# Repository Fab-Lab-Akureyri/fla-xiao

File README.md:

# fla-xiao

KiCad útgáfa af [fabxiao](https://fabacademy.org/2020/labs/leon/students/adrian-torres/fabxiao.html) eftir meistara [Adrián Torres](https://fabacademy.org/2020/labs/leon/students/adrian-torres/index.html).

## Breytingar

- [x] Notast við sökkla fyrir Xiao tölvunar
- [x] Rásum endurrað, hægt að fræsa með 0.4mm bita.
- [x] Íhlutum þjappað aðeins
- [x] .dxf skrá bætt við, hentug fyrir Xtool laser 

## BOM / Íhlutalisti

Hægt að nota 3+4 sökkla fyrir tölvuna eða klippa niður lengri sökkla. 

| Íhlutir               | Magn  |
| ---                   | ---   |
| FR1 bretti            | 1 stk | 
| [ESP32C3](https://www.digikey.fi/en/products/detail/seeed-technology-co-ltd/113991054/16652880) / [RP2040](https://www.digikey.com/en/products/detail/seeed-technology-co-ltd/102010428/14672129) | 1 stk |
| [0Ω](https://www.digikey.com/en/products/detail/yageo/RC1206FR-070RL/5698945) viðnám             | 1 stk |
| [499Ω](https://www.digikey.com/en/products/detail/yageo/RC1206FR-07499RL/728944) viðnám           | 1 stk |
| [1kΩ](https://www.digikey.com/en/products/detail/yageo/RC1206FR-071KL/728387) viðnám            | 1 stk |
| 1026 LED, t.d. [blá](https://www.digikey.com/en/products/detail/nextgen-components/1206BBD8100S01/14318403?s=N4IgjCBcoMwOxVAYygMwIYBsDOBTANCAPZQDaIMATAAwAstEAuoQA4AuUIAymwE4CWAOwDmIAL6EAtLUQgUkDDgLEyIAGwwArJpCMxEkJVVgaagASZcAEzPYAtld1igA)                   | 1 stk |
| [B3SN-takki](https://www.digikey.com/en/products/detail/omron-electronics-inc-emc-div/B3SN-3012/1811776?s=N4IgTCBcDaIM4HcCMSAsYC0A7AJiAugL5A)            | 1 stk |
| [Sökkull 4pos](https://www.digikey.com/en/products/detail/sullins-connector-solutions/NPTC041KFXC-RC/776054)          | 2 stk |
| [Sökkull 3pos](https://www.digikey.com/en/products/detail/sullins-connector-solutions/NPTC031KFXC-RC/776053)          | 2 stk |
| [90° tengi 8 pos](https://www.digikey.com/en/products/detail/samtec-inc/SMH-108-02-G-S/10218741)         | 1 stk |
| [90° tengi 5 pos](https://www.digikey.com/en/products/detail/samtec-inc/SMH-105-02-G-S/10218735) | 1 stk |
| [90° tengi 6 pos](https://www.digikey.com/en/products/detail/gct/BG300-06-A-L-A/9859597) | Hægt að nota í staði 5 pos |

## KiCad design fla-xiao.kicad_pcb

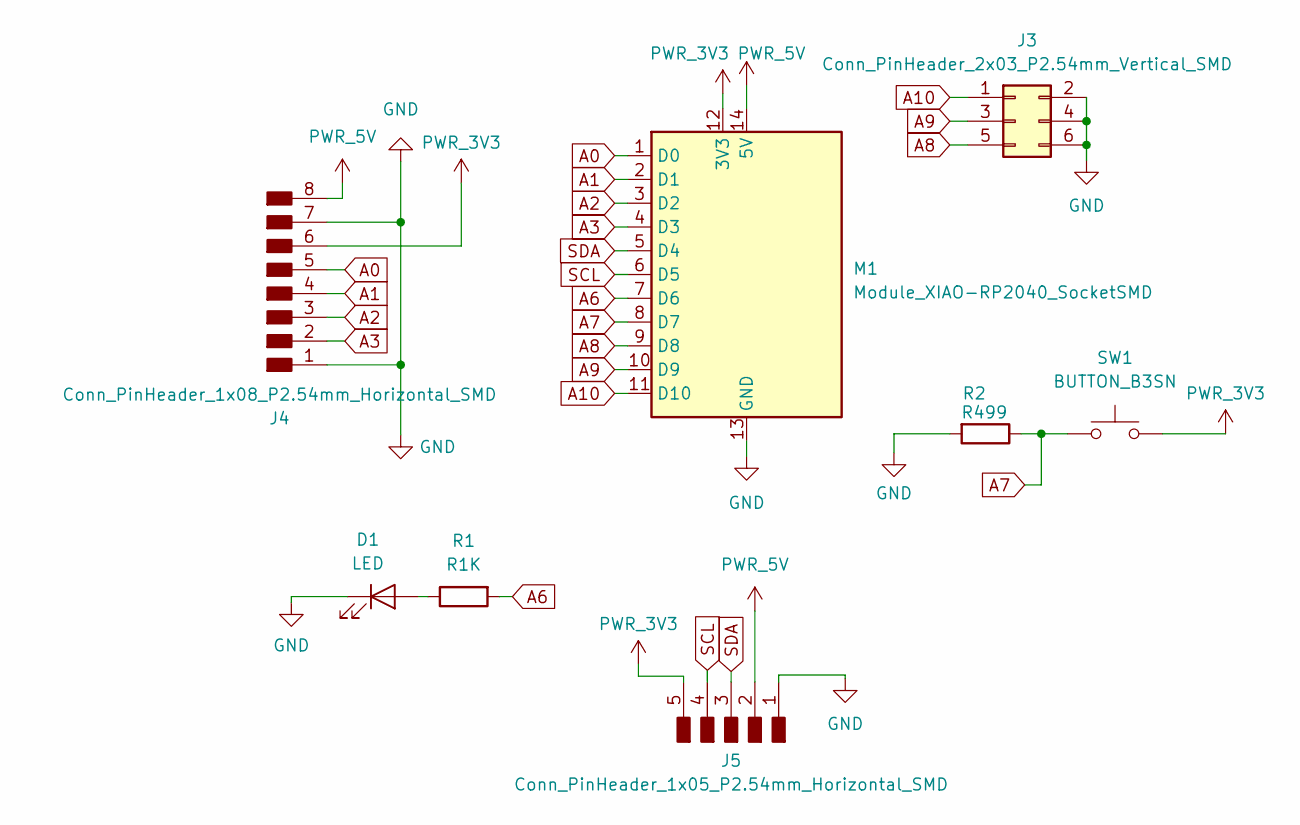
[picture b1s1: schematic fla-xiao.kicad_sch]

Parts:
D1: LED; LED_1206
J3: Conn_PinHeader_2x03_P2.54mm_Vertical_SMD; PinHeader_2x03_P2.54mm_Vertical_SMD
J4: Conn_PinHeader_1x08_P2.54mm_Horizontal_SMD; PinHeader_1x08_P2.54mm_Horizontal_SMD
J5: Conn_PinHeader_1x05_P2.54mm_Horizontal_SMD; PinHeader_1x05_P2.54mm_Horizontal_SMD
M1: Module_XIAO-RP2040_SocketSMD; SeeedStudio_XIAO_SocketSMD
R1: R1K; R_1206
R2: R499; R_1206
SW1: BUTTON_B3SN; Button_Omron_B3SN_6.0x6.0mm

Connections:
A0: J4.5, M1.1 (D0)
A1: J4.4, M1.2 (D1)
A2: J4.3, M1.3 (D2)
A3: J4.2, M1.4 (D3)
A6: M1.7 (D6), R1.2
A7: M1.8 (D7), R2.1, SW1.1
A8: J3.5, M1.9 (D8)
A9: J3.3, M1.10 (D9)
A10: J3.1, M1.11 (D10)
GND: D1.1 (K), J3.2, J3.4, J3.6, J4.1, J4.7, J5.1, M1.13 (GND), R2.2
unnamed: D1.2 (A), R1.1
PWR_3V3: J4.6, J5.5, M1.12 (3V3), SW1.2
PWR_5V: J4.8, J5.2, M1.14 (5V)
SCL: J5.4, M1.6 (D5)
SDA: J5.3, M1.5 (D4)

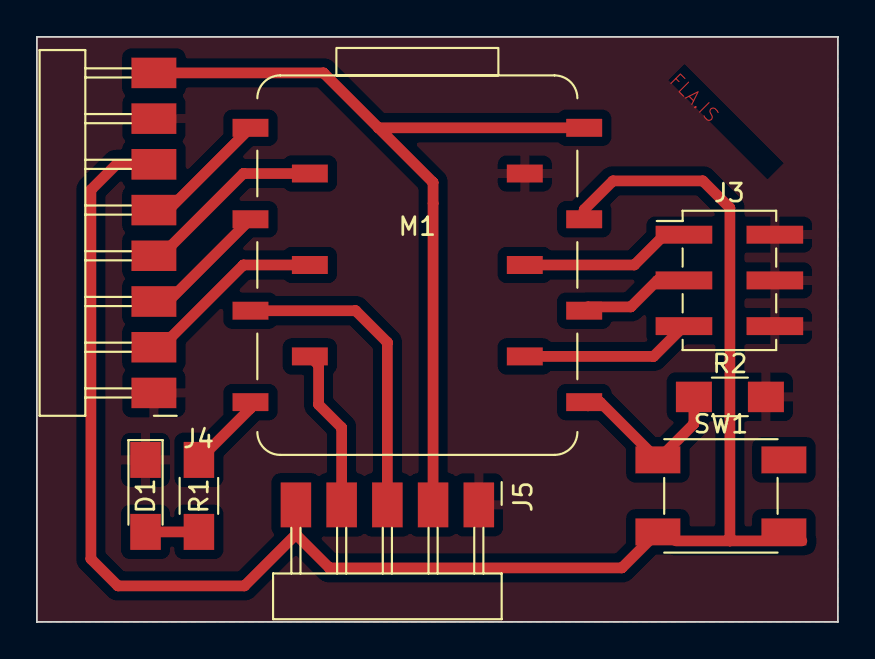
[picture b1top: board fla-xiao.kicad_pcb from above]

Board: 2 copper layers, 44.5 x 32.5 mm, 8 parts (0 on the bottom side), 15 nets.

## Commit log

2023-05-04 Added KiCAD project
2023-05-04 Added images
2023-05-08 Updated to use sockets with XIAO
2023-05-09 .\fla-xiao.kicad*
2023-05-09 Moved a couple of wires, need to clean up
2023-08-31 Updated board
2023-08-31 Updated images
2023-09-01 Fix trace, too close
2023-09-01 Adjust trace and updated image
2023-09-01 Added gerber files to .gitignore
2023-09-01 Updated image and FLA text
2023-09-06 Minor tweaks, updated image
2023-10-03 Update README.md
    Fjarlægði TODO
2023-10-03 Fixed routing
2023-10-05 Uppfærði mynd
2025-10-16 Updated design, for Xtool Laser
2025-10-16 DXF ftw!
2025-10-28 Testing https://github.com/linalinn/kicad-render
2025-10-28 Haetti vid thetta
2025-10-28 Nyjar myndir
2025-10-28 xtool
